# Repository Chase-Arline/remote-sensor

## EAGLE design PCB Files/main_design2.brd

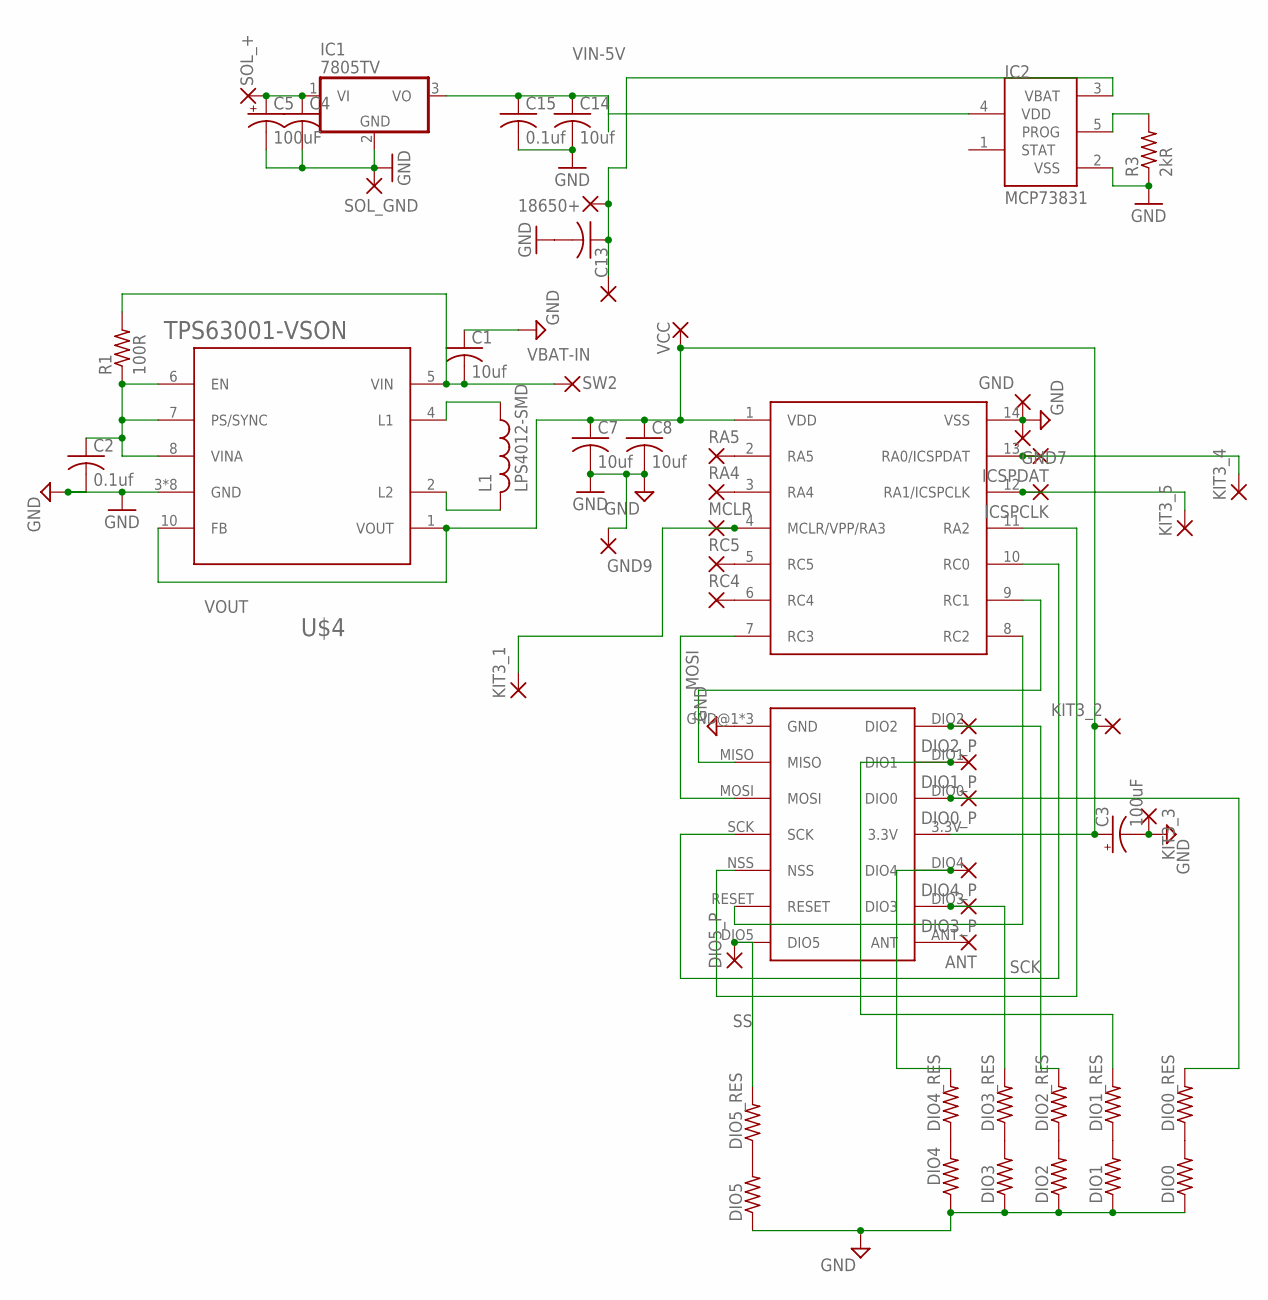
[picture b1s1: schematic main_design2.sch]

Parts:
18650+: 1,6/0,8
ANT: 1,6/0,8
C1, C7, C8, C14: 10uf; C0805
C2, C15: 0.1uf; C0805
C3: 100uF; E5-5
C4: C-USC0402; C0402
C5: 100uF; E5-6
C13: C-USC0805; C0805
DIO0, DIO0_RES, DIO1, DIO1_RES, DIO2, DIO2_RES, DIO3, DIO3_RES, DIO4, DIO4_RES, DIO5, DIO5_RES: R-US_R0805; R0805
DIO0_P, DIO1_P, DIO2_P, DIO3_P, DIO4_P, DIO5_P: 1,6/0,8
GND, GND7, GND9: 1,6/0,8
IC1: 7805TV; TO220V
IC2: MCP73831; SOT23-5L
ICSPCLK: 1,6/0,8
ICSPDAT: 1,6/0,8
KIT3_1, KIT3_2, KIT3_3, KIT3_4, KIT3_5: 1,6/0,8
L1: LPS4012-SMD; LPS4012-222MRC
MCLR: 1,6/0,8
R1: 100R; R0805
R3: 2kR; 0204/7
RA4, RA5: 1,6/0,8
RC4, RC5: 1,6/0,8
SOL_+: 1,6/0,8
SOL_GND: 1,6/0,8
SW1, SW2: 1,6/0,8
U$1: PIC16F1615-TSSOP; PIC16F(L)1615-TSSOP
U$3: RFM69HCW
U$4: TPS63001-VSON
VCC: VCC; 1,6/0,8

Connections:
GND: C1.1, C2.2, C3.-, C4.2, C5.-, C7.2, C8.2, C13.2, C14.2, C15.2, DIO0.1, DIO1.1, DIO2.1, DIO3.1, DIO4.1, DIO5.1, GND.1, GND7.1, GND9.1, IC1.2 (GND), IC2.2 (VSS), KIT3_3.1, R3.1, SOL_GND.1, U$1.14 (VSS), U$3.GND@1 (GND), U$3.GND@2 (GND), U$3.GND@3 (GND), U$4.3 (GND), U$4.9 (GND), U$4.11@0 (GND), U$4.11@1 (GND), U$4.11@2 (GND), U$4.11@3 (GND), U$4.11@4 (GND), U$4.11@5 (GND)
MOSI: U$1.7 (RC3), U$3.MOSI
unnamed: U$1.9 (RC1), U$3.MISO
unnamed: C2.1, R1.1, U$4.6 (EN), U$4.7 (PS/SYNC), U$4.8 (VINA)
unnamed: RA4.1, U$1.3 (RA4)
unnamed: U$1.8 (RC2), U$3.RESET
unnamed: DIO1.2, DIO1_RES.1
unnamed: RA5.1, U$1.2 (RA5)
unnamed: RC5.1, U$1.5 (RC5)
unnamed: RC4.1, U$1.6 (RC4)
unnamed: DIO2_P.1, DIO2_RES.2, U$3.DIO2
unnamed: IC2.5 (PROG), R3.2
unnamed: DIO5.2, DIO5_RES.1
unnamed: ICSPCLK.1, KIT3_5.1, U$1.12 (RA1/ICSPCLK)
unnamed: ICSPDAT.1, KIT3_4.1, U$1.13 (RA0/ICSPDAT)
unnamed: KIT3_1.1, MCLR.1, U$1.4 (MCLR/VPP/RA3)
unnamed: DIO1_P.1, DIO1_RES.2, U$3.DIO1
unnamed: DIO0_P.1, DIO0_RES.2, U$3.DIO0
unnamed: DIO4_P.1, DIO4_RES.2, U$3.DIO4
unnamed: ANT.1, U$3.ANT
unnamed: DIO5_P.1, DIO5_RES.2, U$3.DIO5
unnamed: L1.P$1 (1), U$4.4 (L1)
unnamed: L1.P$2 (2), U$4.2 (L2)
unnamed: DIO4.2, DIO4_RES.1
unnamed: DIO3.2, DIO3_RES.1
unnamed: DIO0.2, DIO0_RES.1
unnamed: DIO2.2, DIO2_RES.1
unnamed: DIO3_P.1, DIO3_RES.2, U$3.DIO3
PRE-BATIN: 18650+.1, C13.1, IC2.3 (VBAT), SW1.1
SCK: U$1.10 (RC0), U$3.SCK
SOL_IN: C4.1, C5.+, IC1.1 (VI), SOL_+.1
SS: U$1.11 (RA2), U$3.NSS
VBAT-IN: C1.2, R1.2, SW2.1, U$4.5 (VIN)
VIN-5V: C14.1, C15.1, IC1.3 (VO), IC2.4 (VDD)
VOUT: C3.+, C7.1, C8.1, KIT3_2.1, U$1.1 (VDD), U$3.3.3V, U$4.1 (VOUT), U$4.10 (FB), VCC.1

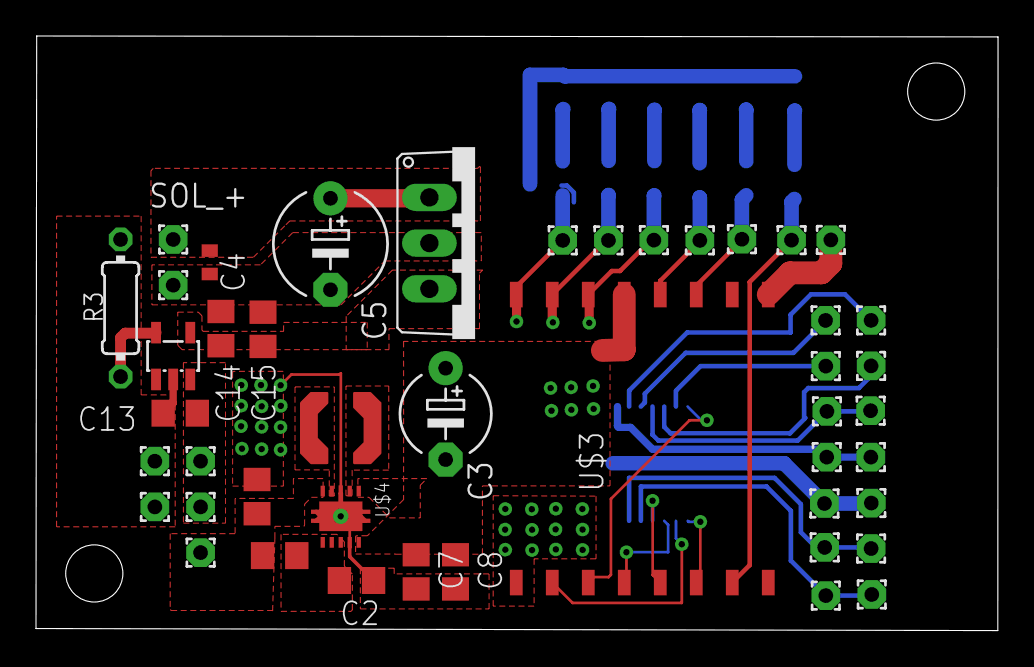
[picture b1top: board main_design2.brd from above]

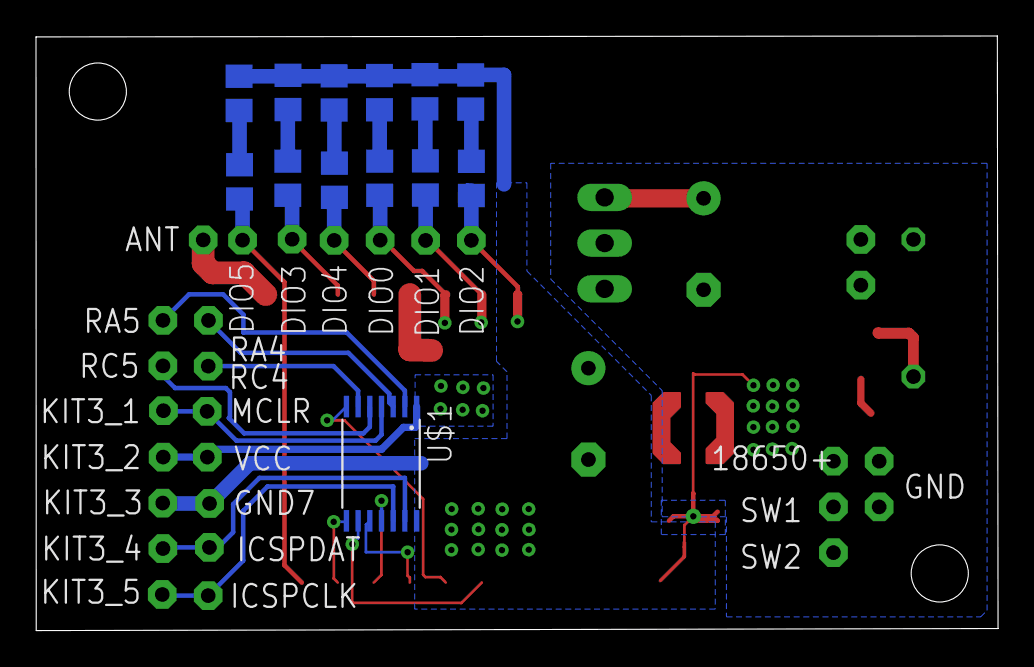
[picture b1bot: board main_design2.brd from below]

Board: 2 copper layers, 53.4 x 33.0 mm, 58 parts (13 on the bottom side), 35 nets.

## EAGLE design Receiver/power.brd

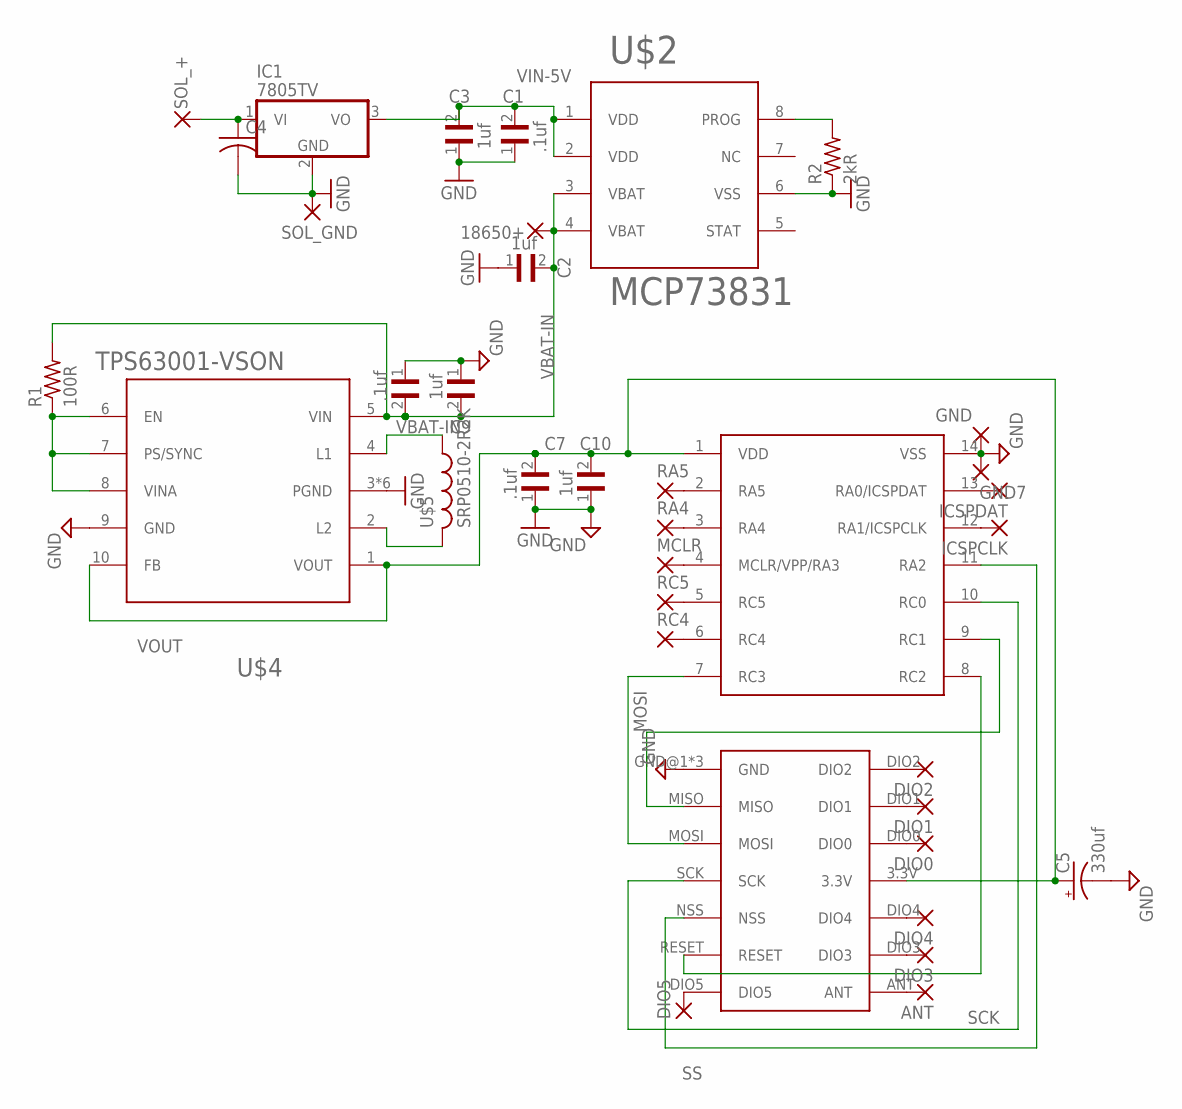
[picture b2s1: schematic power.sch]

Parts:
18650+: 1,6/0,8
ANT: 1,6/0,8
C1, C7: .1uf; CAPC1005X55N
C2, C3, C9, C10: 1uf; CAPC1005X70N
C4: C-USC0402; C0402
C5: 330uf; E5-10,5
DIO0, DIO1, DIO2, DIO3, DIO4, DIO5: 1,6/0,8
GND, GND7: 1,6/0,8
IC1: 7805TV; TO220V
ICSPCLK: 1,6/0,8
ICSPDAT: 1,6/0,8
MCLR: 1,6/0,8
R1: 100R; R0805
R2: 2kR; 0204/7
RA4, RA5: 1,6/0,8
RC4, RC5: 1,6/0,8
SOL_+: 1,6/0,8
SOL_GND: 1,6/0,8
U$1: PIC16F1615-TSSOP; PIC16F(L)1615-TSSOP
U$2: MCP73831; MCP73831-DFN
U$3: RFM69HCW
U$4: TPS63001-VSON
U$5: SRP0510-2R2K
VBAT-IN: .1uf; CAPC1005X55N

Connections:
GND: C1.1, C2.1, C3.1, C4.2, C5.-, C7.1, C9.1, C10.1, GND.1, GND7.1, IC1.2 (GND), R2.1, SOL_GND.1, U$1.14 (VSS), U$2.6 (VSS), U$3.GND@1 (GND), U$3.GND@2 (GND), U$3.GND@3 (GND), U$4.3 (PGND), U$4.9 (GND), U$4.11 (PGND), U$4.11@1 (PGND), U$4.11@2 (PGND), U$4.11@3 (PGND), U$4.11@4 (PGND), VBAT-IN.1
MOSI: U$1.7 (RC3), U$3.MOSI
unnamed: U$1.9 (RC1), U$3.MISO
unnamed: R1.1, U$4.6 (EN), U$4.7 (PS/SYNC), U$4.8 (VINA)
unnamed: RA4.1, U$1.3 (RA4)
unnamed: U$1.8 (RC2), U$3.RESET
unnamed: R2.2, U$2.8 (PROG)
unnamed: RA5.1, U$1.2 (RA5)
unnamed: RC5.1, U$1.5 (RC5)
unnamed: RC4.1, U$1.6 (RC4)
unnamed: DIO2.1, U$3.DIO2
unnamed: ICSPCLK.1, U$1.12 (RA1/ICSPCLK)
unnamed: ICSPDAT.1, U$1.13 (RA0/ICSPDAT)
unnamed: MCLR.1, U$1.4 (MCLR/VPP/RA3)
unnamed: DIO1.1, U$3.DIO1
unnamed: DIO0.1, U$3.DIO0
unnamed: DIO4.1, U$3.DIO4
unnamed: DIO3.1, U$3.DIO3
unnamed: ANT.1, U$3.ANT
unnamed: DIO5.1, U$3.DIO5
unnamed: U$4.4 (L1), U$5.P$1 (1)
unnamed: U$4.2 (L2), U$5.P$2 (2)
SCK: U$1.10 (RC0), U$3.SCK
SOL_IN: C4.1, IC1.1 (VI), SOL_+.1
SS: U$1.11 (RA2), U$3.NSS
VBAT-IN: 18650+.1, C2.2, C9.2, R1.2, U$2.3 (VBAT), U$2.4 (VBAT), U$4.5 (VIN), VBAT-IN.2
VIN-5V: C1.2, C3.2, IC1.3 (VO), U$2.1 (VDD), U$2.2 (VDD)
VOUT: C5.+, C7.2, C10.2, U$1.1 (VDD), U$3.3.3V, U$4.1 (VOUT), U$4.10 (FB)

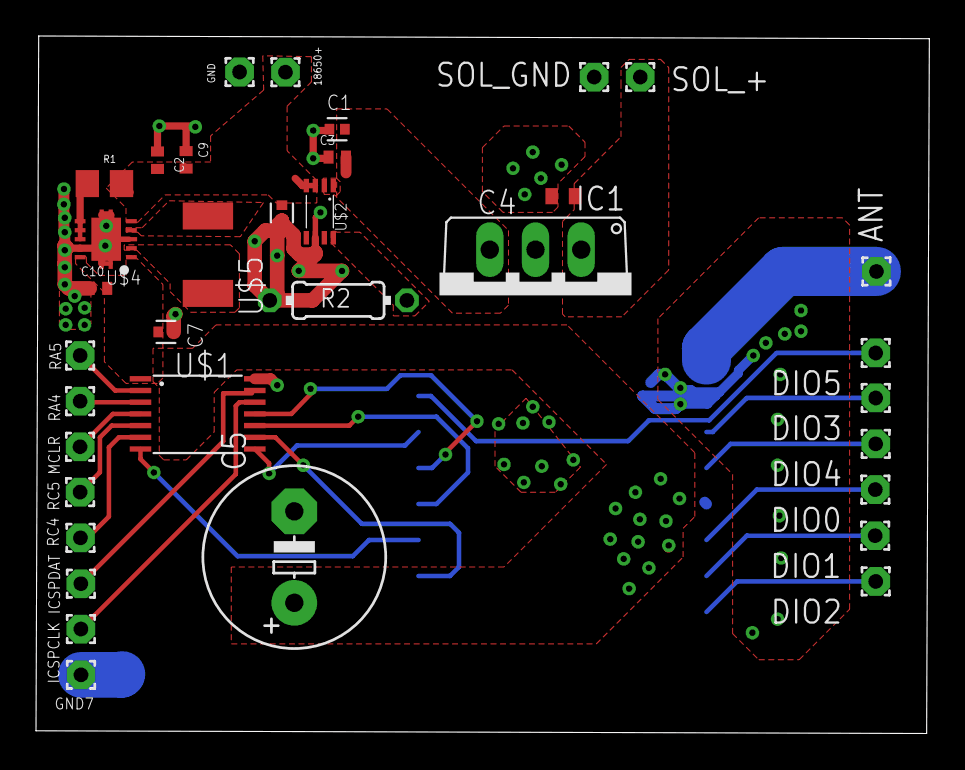
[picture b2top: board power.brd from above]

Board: 2 copper layers, 49.6 x 38.8 mm, 36 parts (1 on the bottom side), 28 nets.

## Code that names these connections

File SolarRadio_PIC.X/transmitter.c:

// PIC16F1615 Configuration Bit Settings

// 'C' source line config statements
// CONFIG1
#pragma config FOSC = INTOSC    // Oscillator Selection Bits (INTOSC oscillator: I/O function on CLKIN pin)
#pragma config PWRTE = OFF      // Power-up Timer Enable (PWRT disabled)
#pragma config MCLRE = ON      // MCLR Pin Function Select (MCLR/VPP pin function is digital input)
#pragma config CP = OFF         // Flash Program Memory Code Protection (Program memory code protection is disabled)
#pragma config BOREN = ON       // Brown-out Reset Enable (Brown-out Reset enabled)
#pragma config CLKOUTEN = OFF   // Clock Out Enable (CLKOUT function is disabled. I/O or oscillator function on the CLKOUT pin)
#pragma config IESO = ON        // Internal/External Switch Over (Internal External Switch Over mode is enabled)
#pragma config FCMEN = ON       // Fail-Safe Clock Monitor Enable (Fail-Safe Clock Monitor is enabled)

// CONFIG2
#pragma config WRT = OFF        // Flash Memory Self-Write Protection (Write protection off)
#pragma config PPS1WAY = ON     // Peripheral Pin Select one-way control (The PPSLOCK bit cannot be cleared once it is set by software)
#pragma config ZCD = OFF        // Zero Cross Detect Disable Bit (ZCD disable.  ZCD can be enabled by setting the ZCDSEN bit of ZCDCON)
#pragma config PLLEN = OFF       // PLL Enable Bit (4x PLL is always enabled)
#pragma config STVREN = ON      // Stack Overflow/Underflow Reset Enable (Stack Overflow or Underflow will cause a Reset)
#pragma config BORV = LO        // Brown-out Reset Voltage Selection (Brown-out Reset Voltage (Vbor), low trip point selected.)
#pragma config LPBOR = OFF      // Low-Power Brown Out Reset (Low-Power BOR is disabled)
#pragma config LVP = OFF    // Low-Voltage Programming Enable (Low-voltage programming enabled)

// CONFIG3
#pragma config WDTCPS = WDTCPS1F// WDT Period Select (Software Control (WDTPS))
#pragma config WDTE = OFF       // Watchdog Timer Enable (WDT enabled)
#pragma config WDTCWS = WDTCWSSW// WDT Window Select (Software WDT window size control (WDTWS bits))
#pragma config WDTCCS = SWC     // WDT Input Clock Selector (Software control, controlled by WDTCS bits)

#include "main.h"
#include "RFM69HCW.h"
#include <xc.h>
#include <math.h>

//Pin Definitions
#define RST PORTCbits.RC2
#define SS PORTAbits.RA2
#define TX_TRIGGER PORTAbits.RA5    
#define THERMISTOR PORTAbits.RA4
#define TH_ENABLE PORTCbits.RC5

//Programmable Constants
#define NODE_ADDR 0x30
#define _XTAL_FREQ 16000000
#define PAYLOAD_LENGTH 4 
#define T0 25.0 //room temp celsius
#define B_COEFF 3950.0 //thermistor coefficient
#define TH_NOM 10000.0 //10k NTC thermistor
#define SERIES_RESISTOR 10000.0 //divider resistor

void spi_init_master();
void resetRadio();
void rfmSetup();

byte rssiThresh = 0;
byte rssi = 0;
byte fifoFlags = 0;
byte modeFlags = 0;
byte powerSettings = 0;
byte operatingMode = 0;
float thermistorTemp;

void TRIS_ANS_Setup() {
    ANSELA = 0; //majority digital connections
    ANSELC = 0; // ^
    TRISC0 = 0; //SPI clock
    TRISC1 = 1; //SPI data input
    TRISC2 = 0; //RESET output to radio
    TRISC3 = 0; //SPI data output
    TRISC5 = 0; //thermistor enable 
    TRISA5 = 1; //tx trigger input
    TRISA2 = 0; // slave select output (unnecessary but still connected for potential future devices outside of PCB))
    TRISA4 = 1; //thermistor divider input
    ANSA4 = 1; // analog input on RA4
}

void analogSetup() {
    //analog reference defaults to VDD as positive reference
    ADFM = 0; //left justified readings (only use ADRESH for 0-255)
    WPUA4 = 0;
}

void resetRadio() {
    RST = 1;
    __delay_ms(1);
    RST = 0;
    __delay_ms(20);
}

int init() {
    TRIS_ANS_Setup();
    analogSetup();
    rfmSetup();
    return 0;
}

void rfmSetup() {
    SSP1BUF;
    SSP1STATbits.BF = 0;
    spi_init_master();
    resetRadio();
    __delay_ms(20);
}

float thermistor_temp() {
    ADCON0bits.CHS = 0b00011; //thermistor A4 on AN3 input
    ADON = 1; //turn ADC on
    TH_ENABLE = 1;
    GO = 1;
    while (GO);
    TH_ENABLE = 0;
    ADON = 0;
    float resistance = TH_NOM / ((255.0 / ADRESH) - 1);
    float temperature = resistance / TH_NOM;
    temperature = log(temperature);
    temperature /= B_COEFF;
    temperature += 1.0 / (T0 + 273.15);
    temperature = 1.0 / temperature;
    temperature -= 273.15;
    return temperature;
}

int main() {
    init();
    RFM69 radio = {.SSport = &PORTA, .SSbit = 2, .node_address = 0x30, .packet_length = PAYLOAD_LENGTH,
        .RSSI_threshold = 0xE4, .sync_words =
        {0x67, 0x67, 0x67, 0x67, 0x67, 0x67, 0x67, 0x67}};
    initRadio(&radio);
    byte *payload = &thermistorTemp;
    setPowerOutput(&radio, POWER_DEFAULT);
    setModulationThreshold(&radio);
    setOperatingMode(&radio, SLEEP_MODE);
    setAutoMode(&radio, 0b01011011); //tx auto modes, fifo level is trigger, packet sent is return to previous state
    while (1) {
        thermistorTemp = thermistor_temp();
        fifoFlags = getFifoFlags(&radio);
        modeFlags = getModeFlags(&radio);
        if (TX_TRIGGER) {
            sendPayload(&radio, payload);
        }
        fifoFlags = getFifoFlags(&radio);
        modeFlags = getModeFlags(&radio);
        __delay_ms(10); //delay for pseudo-hysteresis, implement button press later as an interrupt pin-change
        operatingMode = getOperatingMode(&radio);
        payload[PAYLOAD_LENGTH - 1]++; //increment ascii value by one to discern different messages
    }
    return 0;
}

void spi_init_master() {
    SSP1CON1bits.SSPM = 0b0001;
    SSP1CONbits.SSPEN = 1;
    SSP1CONbits.CKP = 0; //check rfm
    SSP1STATbits.CKE = 1; //check rfm
    SSP1STATbits.SMP = 0; //check rfm (sampling at end of clock)
    //SPI clock select
    RC0PPS = 0b10000;
    //SPI SDI select
    SSPDATPPS = 0b10001;
    //SPI SDO select
    RC3PPS = 0b10001;
}

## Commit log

2020-06-21 init
2020-06-21 almost finished receiver
2020-09-29 power board and sketch
2020-11-24 weird windows addition
2021-07-15 recently printed version, transfer to test on windows mplab
2021-09-12 code replacement, adding boards next
2021-09-12 PCB files for version 1.0
2021-09-20 9.19 new PCB and code is working. currently set to standard power, not H-power versions of RFM69.
